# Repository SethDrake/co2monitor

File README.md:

View this project on [CADLAB.io](https://cadlab.io/node/822). 

# co2monitor

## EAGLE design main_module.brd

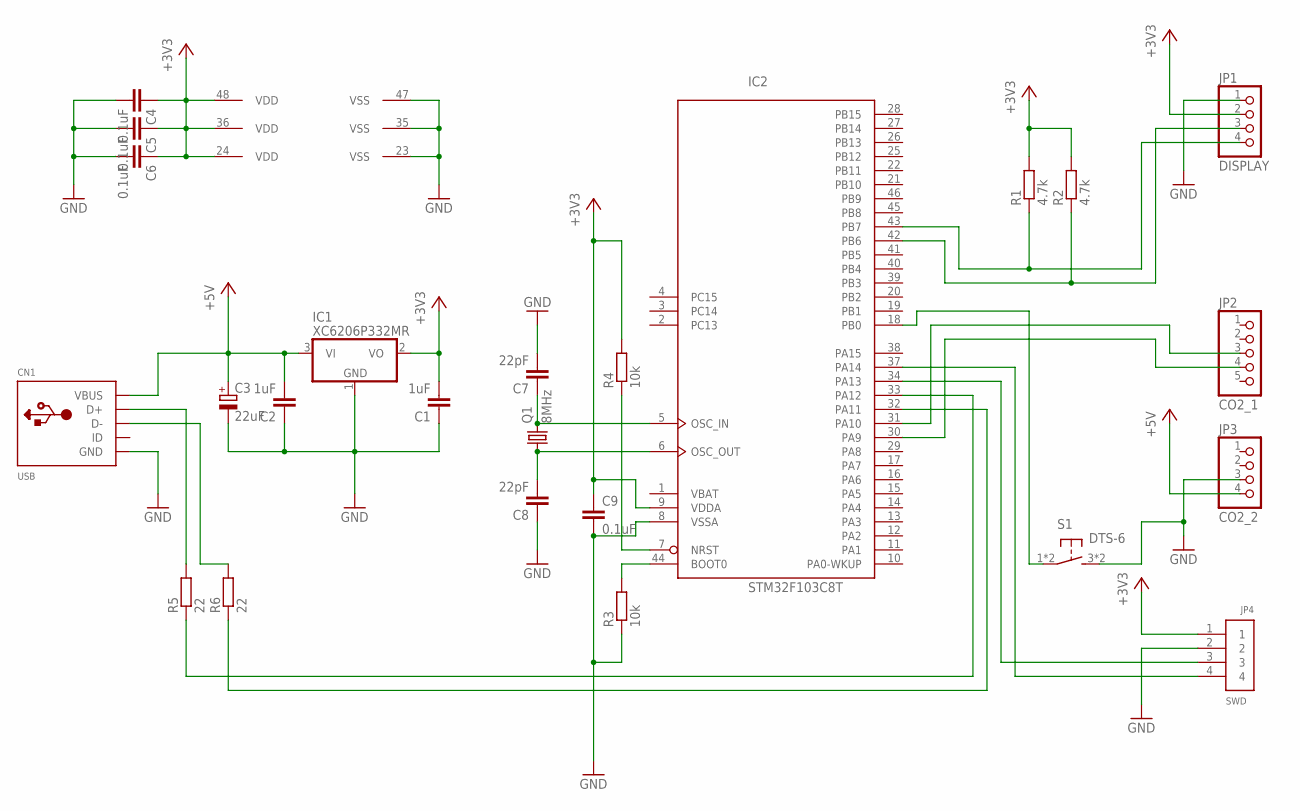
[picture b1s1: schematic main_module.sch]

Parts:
C1, C2: 1uF; C0805
C3: 22uF; C/6032-28R
C4, C5, C6, C9: 0.1uF; C0805
C7, C8: 22pF; C0805
CN1: USB; USB-MINIB
IC1: XC6206P332MR; SOT23
IC2: STM32F103C8T; LQFP48
JP1: DISPLAY; 1X04
JP2: CO2_1; 1X05
JP3: CO2_2; 1X04
JP4: SWD; 1X04-BIG
Q1: 8MHz; HC49UP
R1, R2: 4.7k; R0805
R3, R4: 10k; R0805
R5, R6: 22; R0805
S1: DTS-6

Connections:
+3V3: C1.2, C4.1, C5.1, C6.1, C9.1, IC1.2 (VO), IC2.9 (VDDA), IC2.24 (VDD), IC2.36 (VDD), IC2.48 (VDD), JP1.2, JP4.1, R1.2, R2.2, R4.2
+5V: C2.2, C3.+, CN1.VBUS, IC1.3 (VI), JP3.4
GND: C1.1, C2.1, C3.-, C4.2, C5.2, C6.2, C7.2, C8.1, C9.2, CN1.GND, IC1.1 (GND), IC2.8 (VSSA), IC2.23 (VSS), IC2.35 (VSS), IC2.47 (VSS), JP1.1, JP3.3, JP4.2, R3.1, S1.3, S1.4 (3)
unnamed: C7.1, IC2.5 (OSC_IN), Q1.2
unnamed: IC2.44 (BOOT0), R3.2
unnamed: IC2.18 (PB0), S1.1, S1.2 (1)
unnamed: C8.2, IC2.6 (OSC_OUT), Q1.1
unnamed: IC2.7 (NRST), R4.1
unnamed: CN1.D+, R5.2
unnamed: CN1.D-, R6.2
RX: IC2.31 (PA10), JP2.3
SCL: IC2.42 (PB6), JP1.3, R2.1
SDA: IC2.43 (PB7), JP1.4, R1.1
SWCLK: IC2.37 (PA14), JP4.4
SWDIO: IC2.34 (PA13), JP4.3
TX: IC2.30 (PA9), JP2.4
USB_DM: IC2.32 (PA11), R6.1
USB_DP: IC2.33 (PA12), R5.1
VBAT: IC2.1 (VBAT)

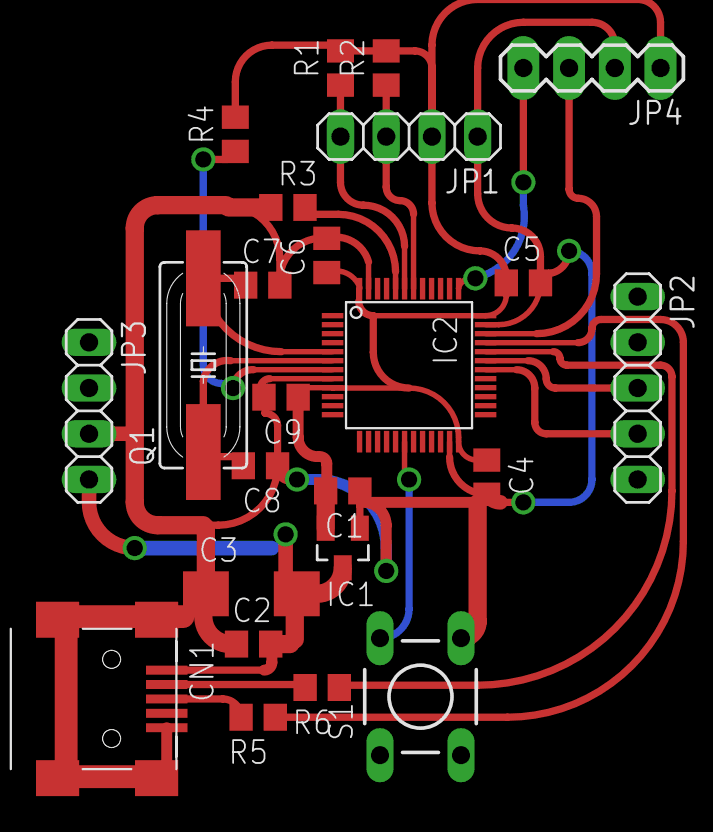
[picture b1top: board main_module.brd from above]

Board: 2 copper layers, 24 parts (0 on the bottom side), 18 nets.

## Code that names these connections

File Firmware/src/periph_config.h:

#pragma once
#ifndef __PERIPH_CONFIG_H_
#define __PERIPH_CONFIG_H_

/* PA13, PA14 - SWD - DON'T USE!!! */
/* PA11, PA12 - USB */

#define I2C_PORT		GPIOB
#define I2C_SCL			GPIO_PIN_6
#define I2C_SDA			GPIO_PIN_7

#define KBRD_PORT		GPIOB
#define KBRD_PIN		GPIO_PIN_0

#define USART_PORT		GPIOA
#define USART_TX	    GPIO_PIN_9
#define USART_RX		GPIO_PIN_10

#endif //__PERIPH_CONFIG_H_

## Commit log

2017-04-18 fix ignores
2018-04-03 Backlink to CADLAB.io has been added.
2018-04-08 updated libs
